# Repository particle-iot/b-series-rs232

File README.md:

# B Series to RS232 bridge
Hardware design repository for B Series to RS232 bridge.

Further Resources:

1. [B402 datasheet](https://docs.particle.io/datasheets/boron/b402-datasheet/)
2. [B523 datasheet](https://docs.particle.io/datasheets/boron/b523-datasheet/)
3. [B Series evaluation board](https://docs.particle.io/datasheets/boron/b-series-eval-board/)
4. [Particle application notes](https://github.com/particle-iot/app-notes)
5. [Hardware libararies and CAD files for Particle devices](https://github.com/particle-iot/hardware-libraries/)
4. [Particle Community](https://community.particle.io/)

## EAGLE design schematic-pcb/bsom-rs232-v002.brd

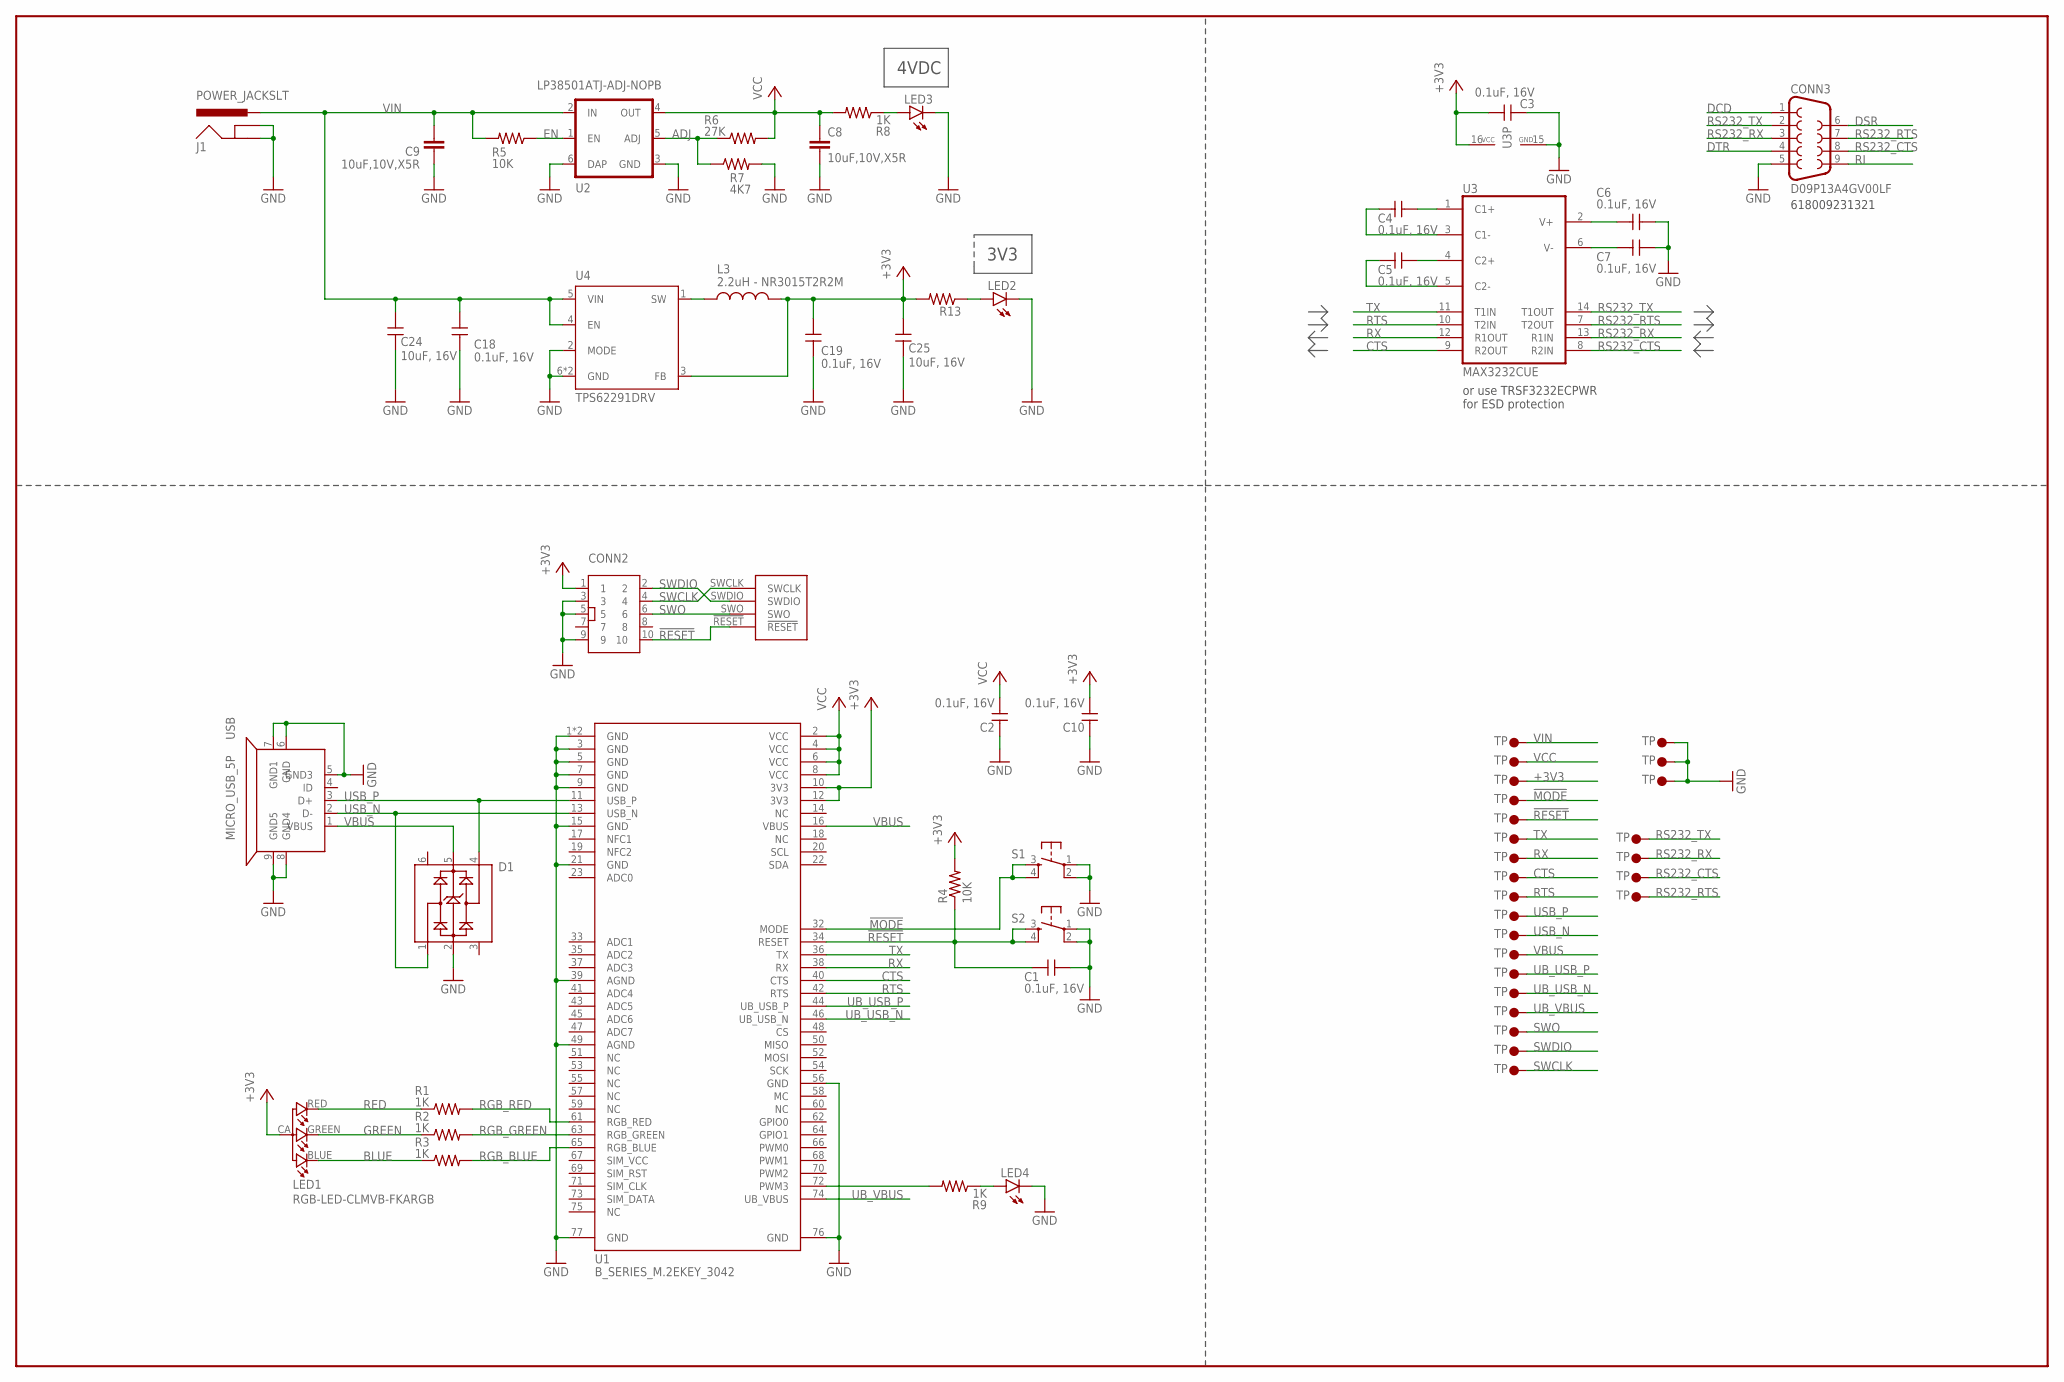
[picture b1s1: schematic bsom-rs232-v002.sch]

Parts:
C1, C2, C3, C4, C5, C6, C7, C10, C18, C19: 0.1uF, 16V; C0603_P
C8, C9: 10uF,10V,X5R; C1206
C24, C25: 10uF, 16V; C0603_P
CONN2: CONN5X2; CONN5X2_1.27; MPN P6014A-M2GC-030-10
CONN3: D09P13A4GV00LF; F09HP
D1: MAX3207EAUT+T; SOT23-6
J1: POWER_JACKSLT; POWER_JACK_SLOT
L3: 2.2uH - NR3015T2R2M; INDUCTOR-NR3015
LED1: RGB-LED-CLMVB-FKARGB; PLCC4-2MM-RGB
LED2, LED3, LED4: LEDCHIP-LED0603; CHIP-LED0603
R1, R2, R3, R8, R9: 1K; R0603_P
R4, R5: 10K; R0603_P
R6: 27K; R0603_P
R7: 4K7; R0603_P
R13: RES_0603; R0603_P
S1, S2: TAC_SWITCHSMD; TACTILE_SWITCH_SMD
U1: B_SERIES_M.2EKEY_3042; PARTICLE_M.2EKEY
U2: LP38501ATJ-ADJ-NOPB; TI_NATIONAL_SEMICONDUCTOR_LP38501ATJ-ADJ-NOPB_0
U3: MAX3232CUE; TSSOP16
U4: TPS62291DRV; S-PWSON-N6
U$1, U$2, U$3, U$4, U$5, U$6, U$7, U$8, U$9, U$10, U$11, U$12, U$13, U$14, U$15, U$16, U$17, U$18, U$19, U$20, U$21, U$22, U$23, U$24, U$25: TP5; TP30_TOP
USB: MICRO_USB_5P; MICRO_USB

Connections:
!MODE: S1.3, S1.4, U1.32 (MODE), U$3.P$1
!RESET: C1.1, CONN2.10, R4.1, S2.3, S2.4, U1.34 (RESET), U1.!RESET, U$4.P$1
+3V3: C3.2, C10.1, C19.1, C25.1, CONN2.1, L3.2, LED1.CA (1), R4.2, R13.2, U1.10 (3V3), U1.12 (3V3), U3.16 (VCC), U4.3 (FB), U$2.P$1
ADJ: R6.1, R7.1, U2.5 (ADJ)
BLUE: LED1.BLUE (2), R3.1
CTS: U1.40 (CTS), U3.9 (R2OUT), U$7.P$1
DCD: CONN3.1
DSR: CONN3.6
DTR: CONN3.4
EN: R5.1, U2.1 (EN)
GND: C1.2, C2.2, C3.1, C6.1, C7.1, C8.2, C9.2, C10.2, C18.2, C19.2, C24.2, C25.2, CONN2.3, CONN2.5, CONN2.9, CONN3.5, D1.2, J1.GND@1 (GNDBREAK), J1.GND@2 (GND), LED2.C, LED3.C, LED4.C, R7.2, S1.1, S1.2, S2.1, S2.2, U1.1 (GND), U1.3 (GND), U1.5 (GND), U1.7 (GND), U1.9 (GND), U1.15 (GND), U1.21 (GND), U1.39 (AGND), U1.49 (AGND), U1.56 (GND), U1.76 (GND), U1.77 (GND), U1.GND, U2.3 (GND), U2.6 (DAP), U3.15 (GND), U4.2 (MODE), U4.6 (GND), U4.TP (GND), U$23.P$1, U$24.P$1, U$25.P$1, USB.5 (GND3), USB.6 (GND), USB.7 (GND1), USB.8 (GND4), USB.9 (GND5)
GREEN: LED1.GREEN (3), R2.1
unnamed: L3.1, U4.1 (SW)
unnamed: LED3.A, R8.1
unnamed: R9.2, U1.72 (PWM3)
unnamed: LED4.A, R9.1
unnamed: C5.1, U3.4 (C2+)
unnamed: C4.1, U3.1 (C1+)
unnamed: C4.2, U3.3 (C1-)
unnamed: C5.2, U3.5 (C2-)
unnamed: C6.2, U3.2 (V+)
unnamed: C7.2, U3.6 (V-)
unnamed: LED2.A, R13.1
RED: LED1.RED (4), R1.1
RGB_BLUE: R3.2, U1.65 (RGB_BLUE)
RGB_GREEN: R2.2, U1.63 (RGB_GREEN)
RGB_RED: R1.2, U1.61 (RGB_RED)
RI: CONN3.9
RS232_CTS: CONN3.8, U3.8 (R2IN), U$21.P$1
RS232_RTS: CONN3.7, U3.7 (T2OUT), U$22.P$1
RS232_RX: CONN3.3, U3.13 (R1IN), U$20.P$1
RS232_TX: CONN3.2, U3.14 (T1OUT), U$19.P$1
RTS: U1.42 (RTS), U3.10 (T2IN), U$8.P$1
RX: U1.38 (RX), U3.12 (R1OUT), U$6.P$1
SIM_VCC: U1.67 (SIM_VCC)
SWCLK: CONN2.4, U1.SWCLK, U$15.P$1
SWDIO: CONN2.2, U1.SWDIO, U$16.P$1
SWO: CONN2.6, U1.SWO, U$17.P$1
TX: U1.36 (TX), U3.11 (T1IN), U$5.P$1
UB_USB_N: U1.46 (UB_USB_N), U$13.P$1
UB_USB_P: U1.44 (UB_USB_P), U$12.P$1
UB_VBUS: U1.74 (UB_VBUS), U$18.P$1
USB_N: D1.1, U1.13 (USB_N), U$10.P$1, USB.2 (D-)
USB_P: D1.4, U1.11 (USB_P), U$9.P$1, USB.3 (D+)
VBUS: D1.5, U1.16 (VBUS), U$11.P$1, USB.1 (VBUS)
VCC: C2.1, C8.1, R6.2, R8.2, U1.2 (VCC), U1.4 (VCC), U1.6 (VCC), U1.8 (VCC), U2.4 (OUT), U$1.P$1
VIN: C9.1, C18.1, C24.1, J1.PWR, R5.2, U2.2 (IN), U4.4 (EN), U4.5 (VIN), U$14.P$1

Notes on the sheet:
or use TRSF3232ECPWR for ESD protection
4VDC
3V3
618009231321

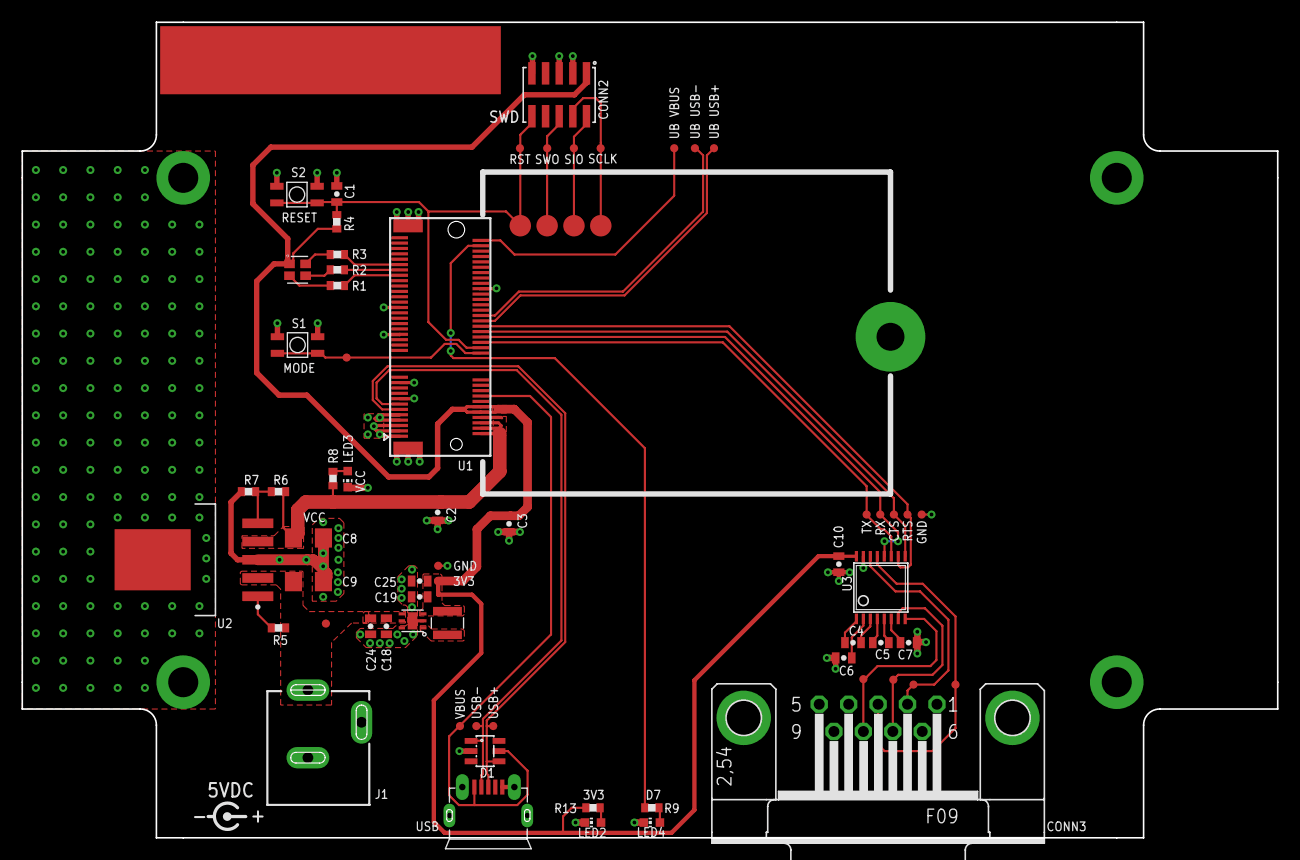
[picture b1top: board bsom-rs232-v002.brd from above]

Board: 2 copper layers, 117.0 x 76.0 mm, 65 parts (0 on the bottom side), 42 nets.

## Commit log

2020-10-23 added schematic, pcb, and gerber files
2020-10-23 added images
